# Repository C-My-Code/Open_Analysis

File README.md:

<!--
SPDX-FileCopyrightText: 2026 Open_Analysis contributors
SPDX-License-Identifier: GPL-3.0-or-later
-->

# Open_Analysis

Open_Analysis is an open-source (GPL-3.0-or-later) analysis suite for KiCad printed circuit boards, with Altium boards supported through import. It covers trace impedance, rule and EMI checks, DC IR drop, and 3D full-wave S-parameters. Signal-integrity (SI) channels, AC power integrity (PI), thermal analysis and EMC pre-compliance are planned.

It is built to answer one question before you pay for fabrication or a compliance test: **how likely is this design to meet its spec?** Every result carries an accuracy class and a stated error, so you can judge how far to trust it. See [How to read results](docs/CONFIDENCE.md).

## Status

Status follows [docs/ROADMAP.md](docs/ROADMAP.md). **Available** means the code runs today and its validation results are on the [validation page](docs/validation/index.md). It does not mean every validation case is closed; open gaps are listed in the next section.

| Feature | Status | Notes |
|---|---|---|
| KiCad 7 to 10 board ingest (`.kicad_pcb`), IPC-2581 ingest | Available | Altium and others through `kicad-cli pcb import` |
| Closed-form trace impedance, 2D BEM, 2D FEM reference | Available | `oa impedance xs`, `oa impedance profile` |
| ERC / EMI rule engine (21 rules registered) | Available | One known validation gap, see below |
| DC IR drop (`pi.dc`) | Available | One rail plus return; multi-rail trees are not done |
| 3D S-parameters with openEMS | Available | Needs openEMS installed. Validated 1 to 10 GHz (microstrip) and 4 to 20 GHz (via) only |
| 3D S-parameters with Palace | In progress | Adapter exists. Its validation cases are pending (WP-301) |
| Own GPU FDTD engine (`oa-fdtd`) | In progress | M1P, gated by [BENCHMARKS.md](docs/BENCHMARKS.md); B-PERF-01 has no engine result yet |
| GPU acceleration (`oa-accel`) | In progress | CuPy backend with a CPU fallback |
| Web UI, REST server, MCP server for AI agents | Available (partly) | Several UI views are not done; see [docs/FOLLOWUPS.md](docs/FOLLOWUPS.md) |
| Linear SI channels (IL/RL/TDR), crosstalk | Planned (M2) | |
| AC PDN, thermal, quasi-static 3D extraction | Planned (M2) | |
| EMC pre-compliance (MIL-STD-461, FCC, CISPR, DO-160) | Planned (M2) | [ADR-0011](docs/adr/0011-emc-compliance-prediction.md) |
| Uncertainty quantification, P(pass) | Planned (M2) | [ADR-0012](docs/adr/0012-uncertainty-quantification.md) |
| KiCad live plugin | Planned (M2) | |

The M1 release is held until the M1P benchmark gates pass (ROADMAP, "M1P").

## Why trust it

The approach is to check every solver against something that is not the solver:

1. **Analytic references** (exact formulas, constructions with a known answer).
2. **Published values** from cited papers, books and standards.
3. **Independent solvers** (BEM against FEM, openEMS against our BEM, one ingest reader against another).
4. **Measured data.** None exists yet.

Rules the validation page follows:

- Every number is produced by `tools/validation/run_validation.py` and stored in [`docs/validation/results.json`](docs/validation/results.json). Nothing is typed by hand.
- Cases whose reference came from this project's own code are labelled *self-computed* and are never counted as independent validation.
- Cases whose citation could not be checked are marked `[verify]` and are excluded from pass counts.
- Known gaps are listed, not hidden. They do not count as passed.

Read: the [validation page](docs/validation/index.md) (also as [HTML](docs/validation/validation.html)), the [benchmark gates](docs/BENCHMARKS.md) and the [known gaps](docs/FOLLOWUPS.md).

### Measured accuracy today

From the run of 2026-10-29 (commit `0cc834dc47ea`, Windows 11, Python 3.13.14; 264 cases: 248 pass, 0 fail, 3 known gap, 2 `[verify]`, 11 pending). "Error" is the absolute difference to the reference, as a percentage unless stated.

| Analysis | Reference | Cases passed | Error (max; median) | Open gap |
|---|---|---|---|---|
| Impedance, closed form and BEM | analytic (Cohn, CPW, wire over plane and others) | 59 (45 with an independent reference) | 0.23 %; 0.02 % (Z0 and eps_eff) | none |
| Impedance, BEM vs 2D FEM | cross-solver (shares the quasi-static model) | 123 of 124 | 0.43 %; 0.06 % | eps_eff on narrow high-er microstrip is 0.58 % off against a 0.5 % spec |
| Impedance, published | IPC-2141 microstrip example | 1 independent pass | 0.06 % (36.82 vs 36.8 ohm) | Polar SI9000, Wadell, Bryant-Weiss tables are pending |
| DC IR, analytic | strip, annulus, via barrel, via array, `power_strip` | 6 of 6 | 0.57 % (via barrel, 1 % tolerance); others 0.06 % or less | `kicad-irdrop` cross-check pending |
| DC IR, raster vs FEM | cross-solver | 3 of 4 | 0.68 % to 0.78 % | as above |
| ERC | one synthetic board per rule | 11 of 12 | exact match | IM-002 on three test boards: the boards miss their own impedance targets |
| Ingest | KiCad vs IPC-2581 readers, counts and areas | 33 of 33 | exact | per-net copper-area checks are partial |
| openEMS microstrip Z0 | our BEM, thin-strip copper | pass | -0.43 % (tolerance 3 %) | against BEM with real 35 um copper: +4.1 %, a **known gap** (openEMS uses sheet copper) |
| openEMS insertion loss, 23 mm microstrip, 10 GHz | our BEM RLGC cascade | pass | 0.089 dB (0.78 vs 0.69 dB; tolerance 0.2 dB) | the M1P target is 0.05 dB |
| Palace, openEMS vs Palace via transition | cross-solver | not run | - | pending WP-301 |

What this table does not say:

- Agreement between BEM and FEM tests the numerics, not the quasi-static assumption both share.
- No result has been compared with a physical measurement yet.
- Material data, tolerances and the stack-up are not in these numbers. See [docs/CONFIDENCE.md](docs/CONFIDENCE.md).

## Install

Requirements:

- Python 3.11 or newer. The repository pins no upper bound; the validation run used 3.13.
- [uv](https://docs.astral.sh/uv/).

```text
git clone <this repository>
cd Open_Analysis
uv sync --all-packages
uv run oa --help
```

### Optional: GPU

GPU support is an extra of the `oa-accel` package and is never a hard dependency. Without it everything runs on the CPU.

```text
uv sync --all-packages --extra cuda12      # NVIDIA, CUDA 12 (cupy-cuda12x, nvmath-python)
```

Extras defined in `packages/oa-accel/pyproject.toml`: `cuda12`, `cuda13`, `rocm`. The extra commands above are not verified on a GPU machine here. Check what was found with `uv run oa-accel-doctor`.

AMD ROCm (`amd-cupy`) is **untested on hardware**. Set `OA_DEVICE=cpu` to force the CPU path.

### Optional: external tools

| Tool | Needed for | Notes |
|---|---|---|
| KiCad 10 (`kicad-cli`) | Altium and other import, DRC, optional zone refill | Found automatically in the usual locations (for example `D:\Program Files\KiCad\*\bin` on Windows, `/usr/bin` on Linux), or set in `tools.toml` |
| openEMS (0.37.x) and its Python bindings | `em.sparams --solver openems` | Run as a separate process, never imported. Path comes from `tools.toml` |
| Palace 0.18.x | `em.sparams --solver palace` | Run in WSL2 or Linux. Build with [`docker/palace/install-wsl.sh`](docker/palace/install-wsl.sh) (no sudo, about 40 minutes, 5 GB of disk), or use [`docker/palace/Dockerfile`](docker/palace/Dockerfile) |

Run `uv run oa doctor` for an offline report of what was found (Python, WSL, Docker, KiCad, gmsh and others). On the machine used to check this README, `oa doctor` found KiCad 10.0.5 and gmsh 4.15.2; openEMS was not installed, so the openEMS solve is not demonstrated below.

### Platform notes

- **Windows (native):** the primary development platform. openEMS runs natively. Palace needs WSL2 or Docker. Process memory is capped by a job object (see TASKS.md, rule 10).
- **Linux:** Palace builds natively with the same script. Tests run on Linux in CI.
- **macOS:** supported for the pure-Python core (ROADMAP: macOS CI covers the core). GPU and external-solver paths are not tested there.

## Quick start

All commands below were run on this repository's test boards. `--json` is an option of each subcommand (write `oa erc --json`, not `oa --json erc`). It prints one envelope: `{schema, version, ok, data, warnings, errors}`.

```text
BOARD=tests/boards/kicad10/microstrip/board.kicad_pcb
```

**Open a board and read it**

```text
uv run oa open $BOARD
uv run oa board summary -p $BOARD
uv run oa board nets -p $BOARD
```

`oa open` returns a `project_id` and a summary. A bare board file opens an ephemeral project and writes nothing next to it. Lengths are in metres.

**Impedance**

```text
uv run oa impedance xs --quick '{"topology":"microstrip","w":"5mil","h":"4mil","t":"1.4mil","er":4.2}'
uv run oa impedance profile -p $BOARD --nets '{"names":["MS_250"]}'
```

The first is the `oa describe` example: a closed-form Hammerstad-Jensen microstrip, which prints Z0 = 58.66 ohm. The second samples net `MS_250` along its route and prints a summary with a `result_id`. Check `accuracy_class` before quoting a number.

**ERC**

```text
uv run oa erc -p $BOARD
uv run oa results summary <result_id>
```

The microstrip board gives 0 violations from 21 rules. Results are stored, so `oa results summary` works from a later command. Use `--fail-on error` for a CI exit code.

**DC IR drop** (on the `power_strip` board, a 50 x 5 mm L1 strip, analytic R = 4.926 mohm)

```text
POWER=tests/boards/kicad10/power_strip/board.kicad_pcb
uv run oa run -p $POWER --analysis pi.dc --config '{"rail":{"net":"STRIP"},"vrm":{"component":"J1","vset":1.0},"loads":[{"component":"J2","current":1.0}]}'
```

This reports the worst load drop and the V, dV and J_mag fields. Run `oa describe --analyses` for the full config schema.

**S-parameters** (3D full wave)

```text
uv run oa run -p $BOARD --analysis em.sparams --dry-run --config '{"solver":"openems","region":{"nets":["MS_250"],"reference_nets":["GND"]},"frequency":{"f_min":1e9,"f_max":1e10,"n_points":50}}'
```

`--dry-run` validates the setup and prints an estimate (3 tasks, about 184 s of work, 1.3 GB peak memory, needs `openems-python`). Remove `--dry-run` to run it once openEMS is installed. The solve itself was not run for this README. Frequencies are numbers in Hz in this form. Output is a Touchstone file that passes a passivity, causality and DC quality gate before it is reported as good.

**Discover everything**

```text
uv run oa describe                 # every command, schema id, side effect, example
uv run oa describe --analyses      # installed analyses with config schemas
uv run oa schema                   # published JSON Schema ids
```

### Web UI

```text
uv run oa serve                    # local REST server and web UI; --port, --host, --no-browser
```

The server binds to 127.0.0.1 with a random bearer token. The front end lives in `web/` (see `web/README.md`). Several result views (TDR, Smith chart, 3D preview) are not done, see FOLLOWUPS.

### Connect an AI agent (MCP)

```text
claude mcp add open-analysis -- uv --directory /path/to/Open_Analysis run oa-mcp --root /path/to/projects
```

`oa-mcp` is a thin adapter over the same command catalog as the CLI. It is read-only unless you ask for a `write` command, and writes go through propose then apply. It makes no network calls; only `oa-assistant` (off by default) may. Details for Claude Code, Claude Desktop and others: [docs/agents/connect.md](docs/agents/connect.md). How an agent should work and state accuracy: [docs/agents/AGENTS.md](docs/agents/AGENTS.md), [docs/agents/accuracy.md](docs/agents/accuracy.md).

## Project layout

```text
packages/    Python packages (uv workspace), layered per docs/ARCHITECTURE.md
  oa-model, oa-framework, oa-geometry, oa-physics, oa-mesh      model and core services
  oa-ingest-kicad, oa-ingest-ipc2581, oa-kicad-bridge           board readers
  oa-impedance, oa-erc, oa-pi, oa-si, oa-thermal, oa-qs, oa-emi analyses (some are skeletons)
  oa-em, oa-em-openems, oa-em-palace, oa-fdtd, oa-accel         3D solvers and GPU backend
  oa-network, oa-results, oa-jobs, oa-service                   S-parameter tools, results, jobs, command catalog
  oa-cli, oa-server, oa-mcp, oa-assistant                       adapters (CLI, REST, MCP, optional AI assistant)
  oa-native, oa-testkit, oa-devguard                            Rust core, test fixtures, dev memory guard
web/         web UI
crates/      Rust sources for oa-native
schemas/     published JSON Schemas
tests/       tests, golden data (tests/golden), test boards (tests/boards)
docs/        architecture, specs, ADRs, roadmap, validation, agent docs
tools/       validation, benchmark and board-generation scripts
docker/      Palace build files
```

Key documents: [ARCHITECTURE](docs/ARCHITECTURE.md), [ROADMAP](docs/ROADMAP.md), [TASKS](docs/TASKS.md), [BENCHMARKS](docs/BENCHMARKS.md), [specs](docs/specs/), [ADRs](docs/adr/).

## Contributing

Read [CLAUDE.md](CLAUDE.md) (or [AGENTS.md](AGENTS.md)) and [docs/TASKS.md](docs/TASKS.md). The rules are binding: owned paths per work package, frozen contracts, SPDX headers on every new file, and a DCO sign-off on every commit.

```text
uv run pytest -m "not external"
uv run ruff check . && uv run ruff format --check .
uv run mypy
uv run lint-imports
uv run reuse lint
```

## License

GPL-3.0-or-later ([LICENSE](LICENSE), [ADR-0001](docs/adr/0001-license-gpl3.md)). The JSON Schemas (`schemas/`), test boards and fixtures (`tests/boards/`, `tests/fixtures/`) and `examples/` are dual-licensed `CC-BY-4.0 OR GPL-3.0-or-later`: recipients choose either (ADR-0001, `REUSE.toml`). Code stays GPL-3.0-or-later.

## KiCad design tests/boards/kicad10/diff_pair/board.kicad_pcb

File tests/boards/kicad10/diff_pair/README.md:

# diff_pair

6-layer board. One 100 ohm class edge-coupled pair DP_P/DP_N: L1 microstrip (3 mm uncoupled breakout, 0.4 mm length mismatch bump), a blind via pair with 4 GND return vias, L3 stripline with a gap step, a second via pair with 4 return vias, and L1 pads.

## Files

- `board.kicad_pcb`, `board.kicad_pro`: the board (KiCad 10 syntax, generated with KiCad 10.0.5).
- `expected.yaml`: ground truth for the readers and analyses (schema: `../expected.schema.json`).
- `drc.json`: `kicad-cli pcb drc --format json --severity-all` output.
- `board.ipc2581.xml`: IPC-2581 rev C export, `board.odb.zip`: ODB++ export, `board.png`: 3D render.

## Deliberate features and their rules

| Rule | Nets | Layer | Location (mm, file frame) | Created by |
|---|---|---|---|---|
| DP-001 | DP_P, DP_N | L1 | 11.500, 15.000 | `boardgen.features.diff_pair` |
| DP-002 | DP_P, DP_N | L1 | - | `boardgen.features.diff_pair` |
| DP-003 | DP_P, DP_N | L3 | 72.500, 15.000 | `boardgen.features.diff_pair` |

## KiCad DRC

0 errors, 0 warnings (`drc.json`). By type: `{}`.

## Regenerate

```
python tools/boardgen/build_all.py --only diff_pair
```

Licence: CC-BY-4.0 (see the `.license` sidecars).

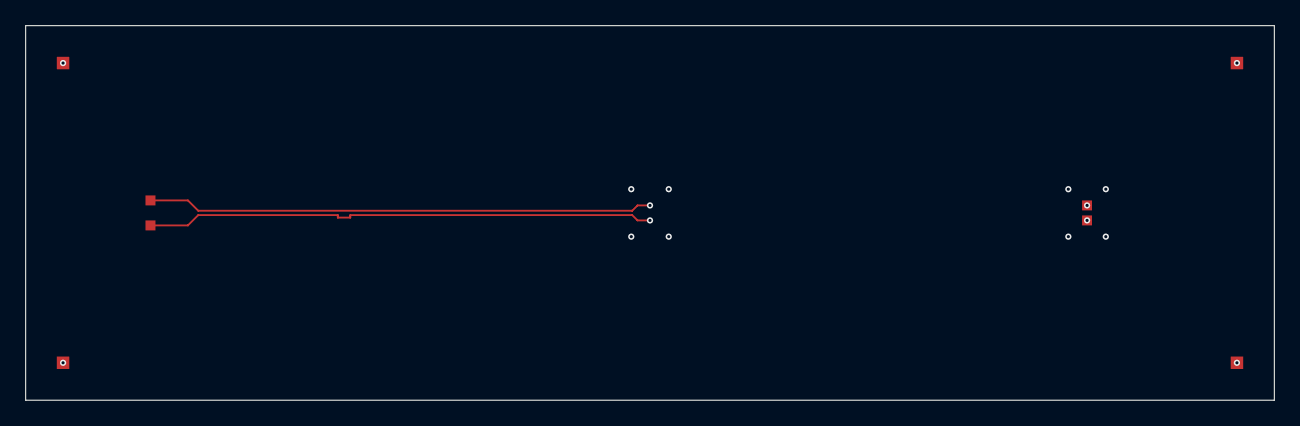
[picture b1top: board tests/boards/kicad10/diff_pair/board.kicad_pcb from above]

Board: 6 copper layers, 100.0 x 30.0 mm, 8 parts (0 on the bottom side), 3 nets.

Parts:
TP1, TP2, TP3, TP4, TP5, TP6, TP7, TP8: OA_Test:Pad; Pad

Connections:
DP_N: TP6.1, TP8.1
DP_P: TP5.1, TP7.1
GND: TP1.1, TP2.1, TP3.1, TP4.1

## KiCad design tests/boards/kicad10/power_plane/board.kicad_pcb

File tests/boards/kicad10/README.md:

# Synthetic KiCad 10 test boards (WP-102)

Eleven small boards with known geometry, written by `tools/boardgen/` and refilled, checked and exported with
KiCad 10.0.5. They are the ground truth for the KiCad reader (WP-101), the IPC-2581 reader (WP-103), the ERC rules
(WP-201), impedance/profile/DC/EM tests and the web viewer. All are FR-4-like (Dk 4.3, Df 0.02), 35 um copper, no
solder mask, with a known stackup. Licence: CC-BY-4.0 (`*.license` sidecars); the generator is GPL-3.0-or-later.

| Directory | Layers | Purpose |
|---|---|---|
| `microstrip` | 4 (1.6 mm) | 3 L1 microstrips (0.25/0.35/0.5 mm, 50 mm, h = 0.2 mm), launch pads; IM-002 on the 0.25 and 0.5 mm traces |
| `microstrip_v9` | 4 | Same copper in KiCad 9 syntax (net table, numeric item nets, version 20241229) |
| `stripline` | 6 | Symmetric stripline on L3, offset stripline on L4 (L3 empty above, L5 GND below) |
| `diff_pair` | 6 | 100 ohm pair: L1 microstrip, blind via pair + 4 return vias, L3 stripline; DP-001/002/003 |
| `cpwg` | 4 | CPWG (S 0.3, G 0.15, h 0.2) with two via fences (RF-001 on the 3x pitch) |
| `split_plane` | 4 | RP-001/002/003/007, ED-001/002 |
| `via_transition` | 8 (2.0 mm) | Stub (VI-001), backdrill, via pair with returns, transition without return (RP-004), blind/buried/micro vias |
| `power_plane` | 4 | L3 +1V0 plane 40 x 30 mm, VRM U5, load U1 (32 pins), decaps C1 (1.5 mm) and C2 (12 mm): PD-001; EM-011 cavity |
| `power_strip` | 4 | 50 x 5 mm strip, analytic R = Rs L / W |
| `power_two_layer_vias` | 4 | Two 20 x 20 mm squares joined by 9 vias, analytic via-array R |
| `combined` | 8 | Everything above in separate regions, net classes `50ohm`/`90ohm`/`100ohm`, `USB_D+`/`USB_D-` |

Every directory holds `board.kicad_pcb`, `board.kicad_pro`, `board.ipc2581.xml` (IPC-2581 rev C),
`board.odb.zip`, `board.png` (3D render), `drc.json`, `expected.yaml` and a `README.md`.

## Regenerate

```
python tools/boardgen/build_all.py                 # all boards (needs KiCad 10.0.5; set OA_KICAD_DIR if not in the default place)
python tools/boardgen/build_all.py --only cpwg     # one board
python tools/boardgen/validate_expected.py         # schema + consistency check (needs pyyaml, jsonschema)
```

Output is deterministic: uuids come from `uuid5(board, kind, counter)` and timestamps are scrubbed, so two runs
give byte-identical `board.kicad_pcb`, `board.kicad_pro`, `drc.json`, `expected.yaml` and `README.md`. The IPC-2581 and
ODB++ exports are KiCad output whose element order (pads within a package, for example) varies from run to run; they
are equal as data, not as bytes, so compare them by parsing. `.gitattributes` here disables line-ending conversion.

## `expected.yaml` (schema: `expected.schema.json`, id `oa-board-expected/1`)

All physical quantities are SI (m, m^2, Hz, S/m, ohm). Exceptions, named `*_mm`: positions and tolerances in millimetres
in the **KiCad file frame (Y down)**; the Y-up board model uses `y_model = -y_file`. Layer ids are canonical (`L1` = top
copper, `D1` = first dielectric, top to bottom); `source_layer`/`source_name` give the KiCad name. z = 0 is the bottom face
of the lowest copper layer.

| Key | Content |
|---|---|
| `kicad` | syntax flavour (10/9), file version, whether a net table exists |
| `materials` | Dk, Df, copper thickness, conductivity (5.8e7 S/m, the model default) |
| `counts` | nets, vias per kind (`through`/`blind`/`buried`/`micro`), pads (smd/tht), tracks, arcs, zones, rule areas (copper-pour keepouts), footprints, copper layers. Measured by pcbnew after the refill and asserted equal to the generator's own count |
| `stackup` | `board_thickness` and per-layer `thickness`, `z_bottom`, `z_top` (exact to 1 nm) |
| `copper_area` | per layer, per net, m^2, computed by pcbnew after `ZONE_FILLER` (union of fills, tracks, pads, via pads); tolerance 0.1 % |
| `nets`, `net_classes`, `net_class_patterns`, `diff_pairs` | net names, `.kicad_pro` classes/patterns, pair membership (`origin`: `naming`) |
| `geometry` | named dimensions per feature (widths, lengths, gaps, via spans, stub lengths, plane outlines, ...) |
| `erc` | violations that MUST be reported: `rule_id`, `nets`, `layer`, `location_mm` (null = whole-net result), `tolerance_mm`, `generator` (the `boardgen.features.*` function that created the feature) and `why` |
| `must_not_report` | catalogue rules that must not fire anywhere on the board |
| `negative_cases` | specific places that look similar but are compliant (a test may assert no report there) |
| `unspecified` | cases where the result depends on rule thresholds; tests must not assert either way |
| `intended_drc` | KiCad DRC **errors** that are deliberate (empty on every board) |
| `drc` | counts and types of all DRC results, including warnings |
| `dc` | analytic resistances with formula and tolerance (`power_strip`, `power_two_layer_vias`) |
| `em` | EM-011 cavity frequencies and suggested ports (`power_plane`) |

## Using KiCad on these boards

DRC: `kicad-cli pcb drc --format json --severity-all board.kicad_pcb` returns exit code 0 and 0 errors on every board.
Remaining warnings are `via_dangling` (isolated buried/blind/micro vias that exist only to exercise the reader and the
swiss-cheese antipads). Loading a board with `pcbnew.LoadBoard` from Python can block on a wx assertion dialog for
some inputs (seen with the KiCad 9 syntax file); always run such helpers with a timeout.

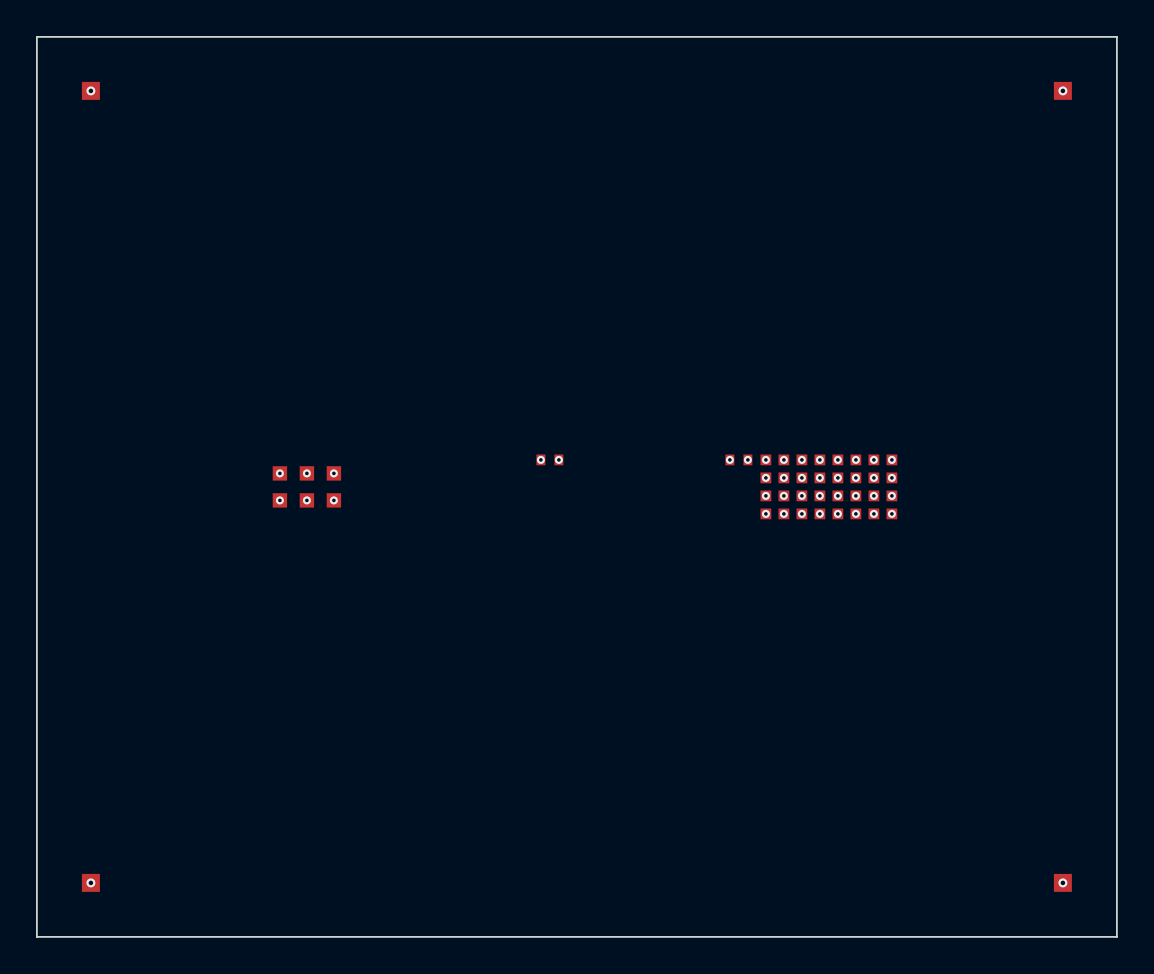
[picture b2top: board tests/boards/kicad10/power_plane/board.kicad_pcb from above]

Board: 4 copper layers, 60.0 x 50.0 mm, 8 parts (0 on the bottom side), 2 nets, no tracks yet.

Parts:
C1, C2: OA_Test:C_0402; C_0402
TP1, TP2, TP3, TP4: OA_Test:Pad; Pad
U1: OA_Test:Load_8x4; Load_8x4
U5: OA_Test:VRM_3out; VRM_3out

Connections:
+1V0: C1.2, C2.2, U1.1, U1.3, U1.6, U1.8, U1.9, U1.11, U1.14, U1.16, U1.17, U1.19, U1.22, U1.24, U1.25, U1.27, U1.30, U1.32, U5.1, U5.2, U5.3
GND: C1.1, C2.1, TP1.1, TP2.1, TP3.1, TP4.1, U1.2, U1.4, U1.5, U1.7, U1.10, U1.12, U1.13, U1.15, U1.18, U1.20, U1.21, U1.23, U1.26, U1.28, U1.29, U1.31, U5.4, U5.5, U5.6

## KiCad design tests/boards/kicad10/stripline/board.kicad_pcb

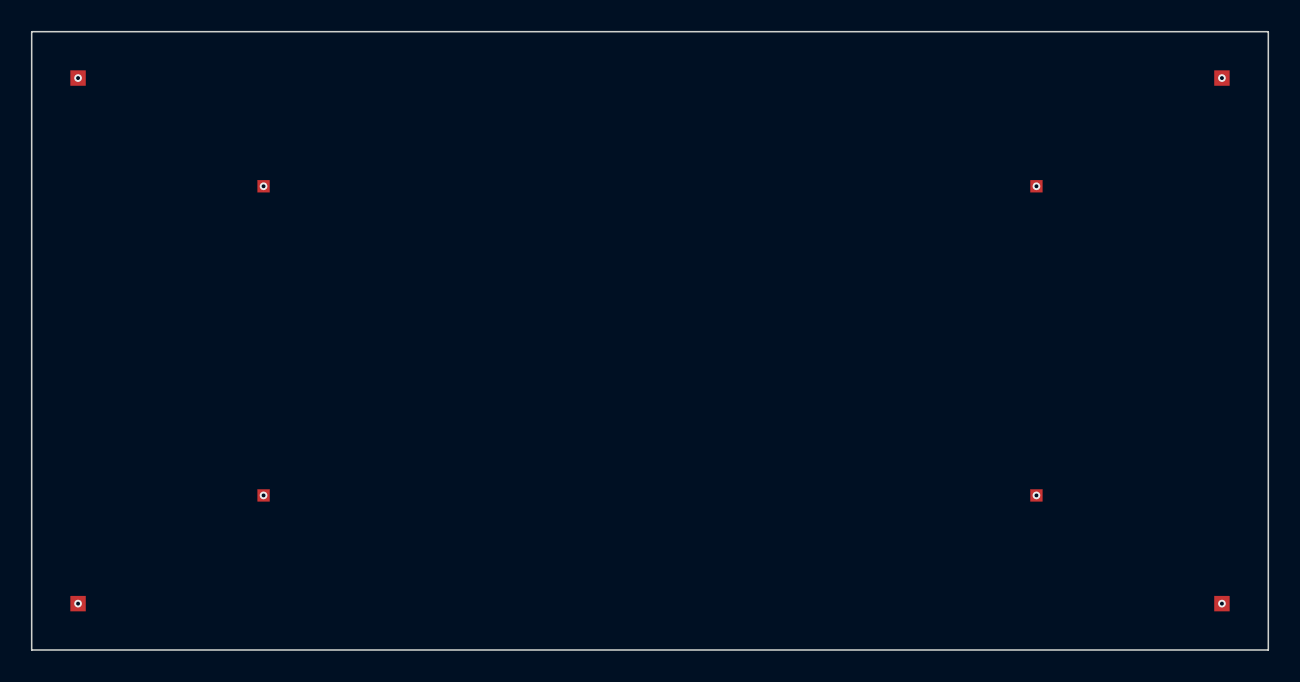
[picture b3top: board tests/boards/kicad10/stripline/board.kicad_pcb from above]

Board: 6 copper layers, 80.0 x 40.0 mm, 8 parts (0 on the bottom side), 3 nets.

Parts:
TP1, TP2, TP3, TP4, TP5, TP6, TP7, TP8: OA_Test:Pad; Pad

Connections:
GND: TP1.1, TP2.1, TP3.1, TP4.1
SL_OFF: TP7.1, TP8.1
SL_SYM: TP5.1, TP6.1

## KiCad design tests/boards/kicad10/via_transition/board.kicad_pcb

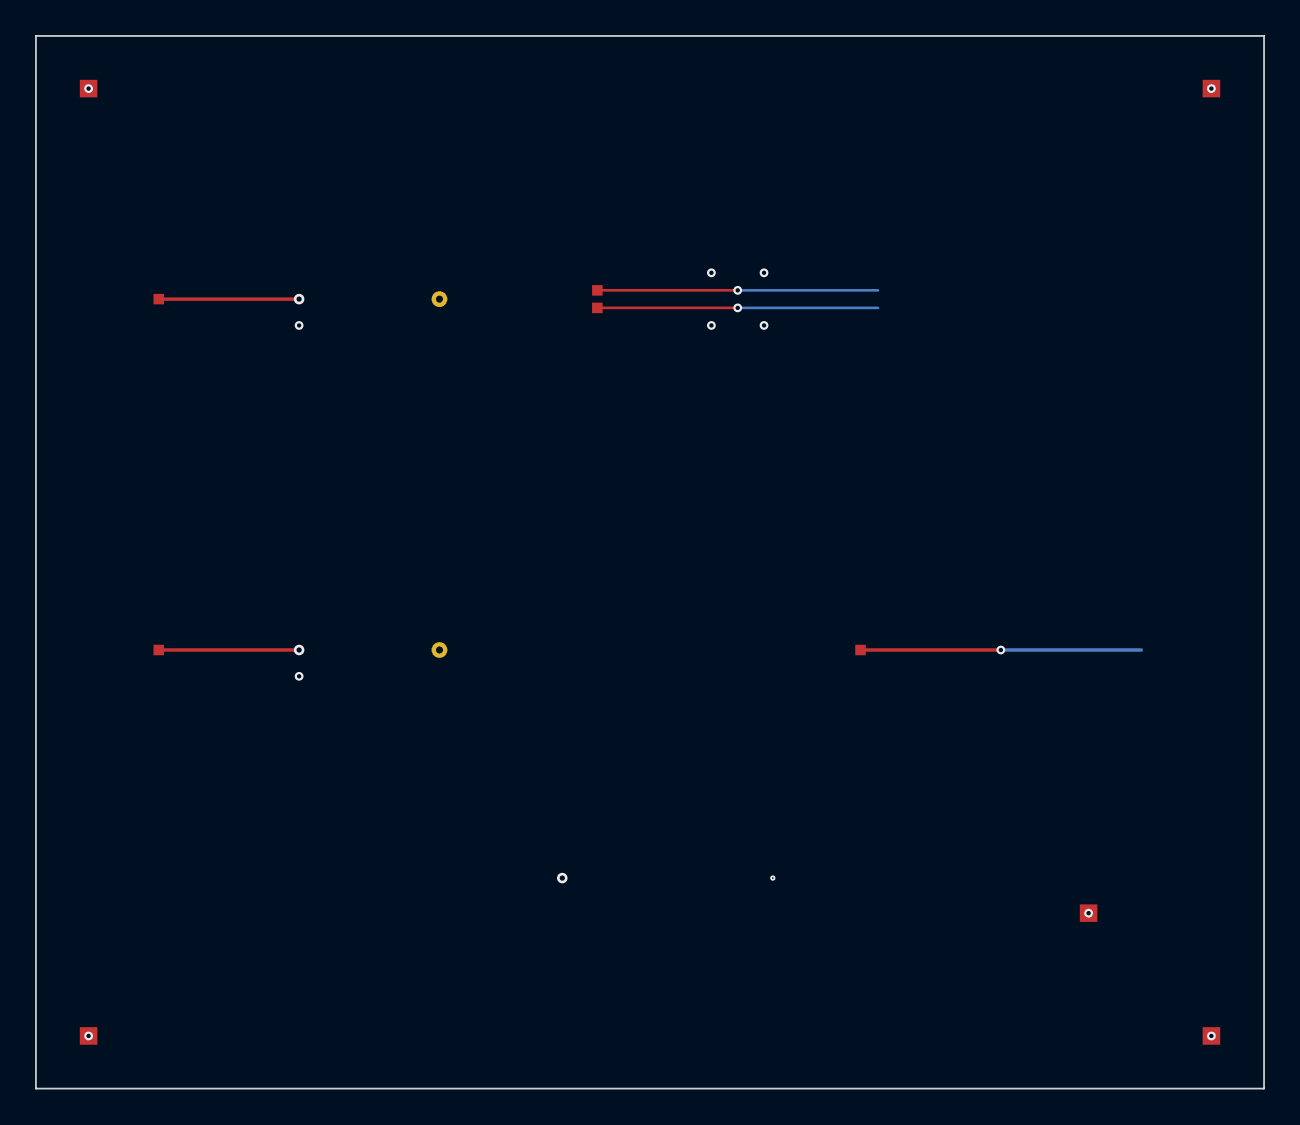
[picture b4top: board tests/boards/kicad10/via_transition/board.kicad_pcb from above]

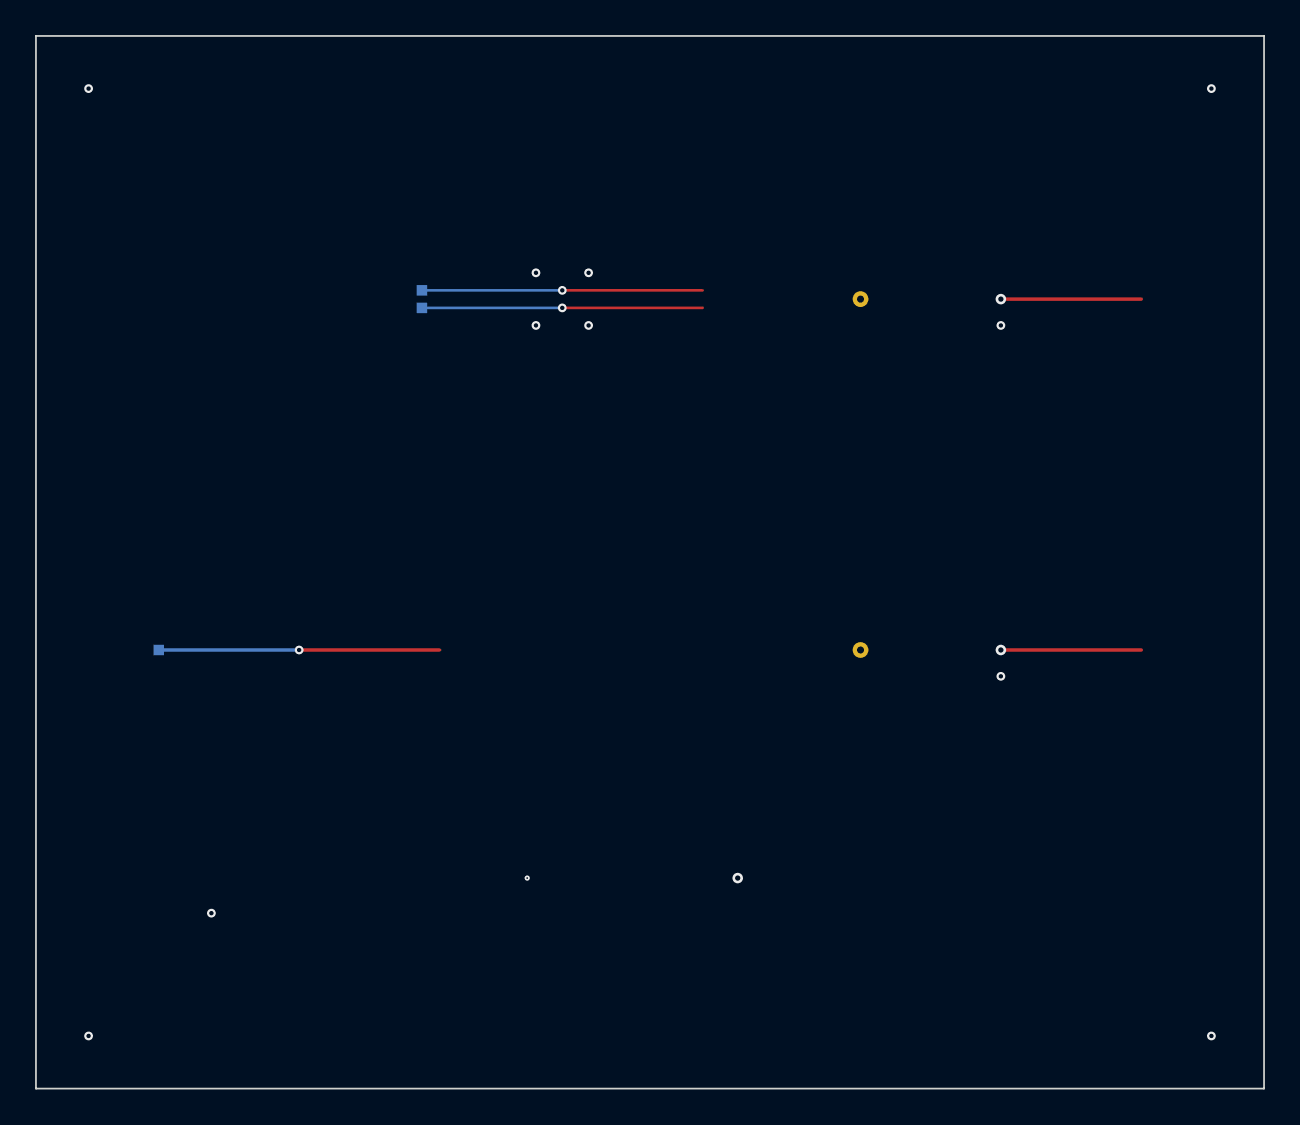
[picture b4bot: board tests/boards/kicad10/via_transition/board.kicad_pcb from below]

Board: 8 copper layers, 70.0 x 60.0 mm, 15 parts (3 on the bottom side), 6 nets.

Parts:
TH1, TH2: OA_Test:Pad; Pad
TP1, TP2, TP3, TP4, TP5, TP6, TP7, TP8, TP9, TP10, TP11, TP12, TP13: OA_Test:Pad; Pad

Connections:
GND: TP1.1, TP2.1, TP3.1, TP4.1
NR: TP12.1, TP13.1
SE1: TH1.1, TP6.1
SE2: TH2.1, TP7.1
VD_N: TP10.1, TP11.1
VD_P: TP8.1, TP9.1

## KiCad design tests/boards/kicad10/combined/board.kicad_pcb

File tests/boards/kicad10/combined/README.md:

# combined

8-layer 2.0 mm board carrying every violation of the other boards in separate regions, plus net classes 50ohm / 90ohm / 100ohm and the USB_D+ / USB_D- pair. L2/L4/L7 GND planes, L5 +1V0 plane (full board).

## Files

- `board.kicad_pcb`, `board.kicad_pro`: the board (KiCad 10 syntax, generated with KiCad 10.0.5).
- `expected.yaml`: ground truth for the readers and analyses (schema: `../expected.schema.json`).
- `drc.json`: `kicad-cli pcb drc --format json --severity-all` output.
- `board.ipc2581.xml`: IPC-2581 rev C export, `board.odb.zip`: ODB++ export, `board.png`: 3D render.

## Deliberate features and their rules

| Rule | Nets | Layer | Location (mm, file frame) | Created by |
|---|---|---|---|---|
| RP-001 | SIG_SLOT | L1 | 50.000, 15.000 | `boardgen.features.split_plane` |
| ED-001 | SIG_PLEDGE | L1 | 30.000, 51.750 | `boardgen.features.split_plane` |
| RP-007 | SIG_NOREF | L1 | 75.000, 56.000 | `boardgen.features.split_plane` |
| RP-002 | SIG_SWISS | L1 | 20.000, 30.000 | `boardgen.features.split_plane` |
| RP-003 | SIG_REFCHG | L1 | 75.000, 35.000 | `boardgen.features.split_plane` |
| ED-002 | SIG_BOARDEDGE | L1 | 0.400, 25.000 | `boardgen.features.split_plane` |
| IM-002 | MS_250 | L1 | 135.000, 10.000 | `boardgen.features.microstrip` |
| IM-002 | MS_500 | L1 | 135.000, 30.000 | `boardgen.features.microstrip` |
| RF-001 | CPW_B | L1 | 195.000, 30.000 | `boardgen.features.cpwg` |
| VI-001 | SE1 | L6 | 15.000, 90.000 | `boardgen.features.via_transition` |
| RP-004 | NR | L1 | 55.000, 110.000 | `boardgen.features.via_transition` |
| DP-001 | DP_P, DP_N | L1 | 81.500, 100.000 | `boardgen.features.diff_pair` |
| DP-002 | DP_P, DP_N | L1 | - | `boardgen.features.diff_pair` |
| DP-003 | DP_P, DP_N | L3 | 142.500, 100.000 | `boardgen.features.diff_pair` |
| PD-001 | +1V0 | L1 | 198.500, 98.500 | `boardgen.features.power_loads` |

## Notes

- KiCad has no explicit diff-pair object: the Altium-style explicit pair is represented by the +/- naming and the 90ohm netclass pattern USB_D*.

## KiCad DRC

0 errors, 28 warnings (`drc.json`). By type: `{"warning": {"via_dangling": 28}}`.

## Regenerate

```
python tools/boardgen/build_all.py --only combined
```

Licence: CC-BY-4.0 (see the `.license` sidecars).

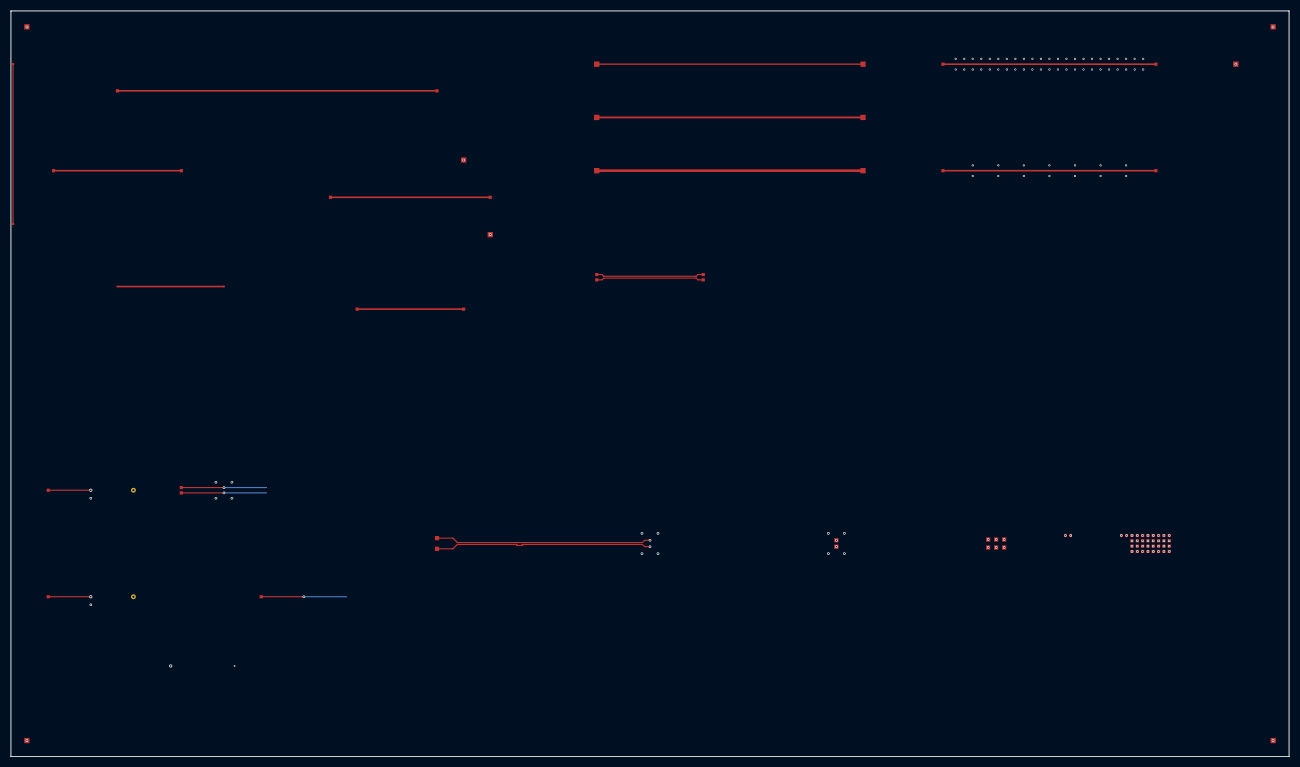
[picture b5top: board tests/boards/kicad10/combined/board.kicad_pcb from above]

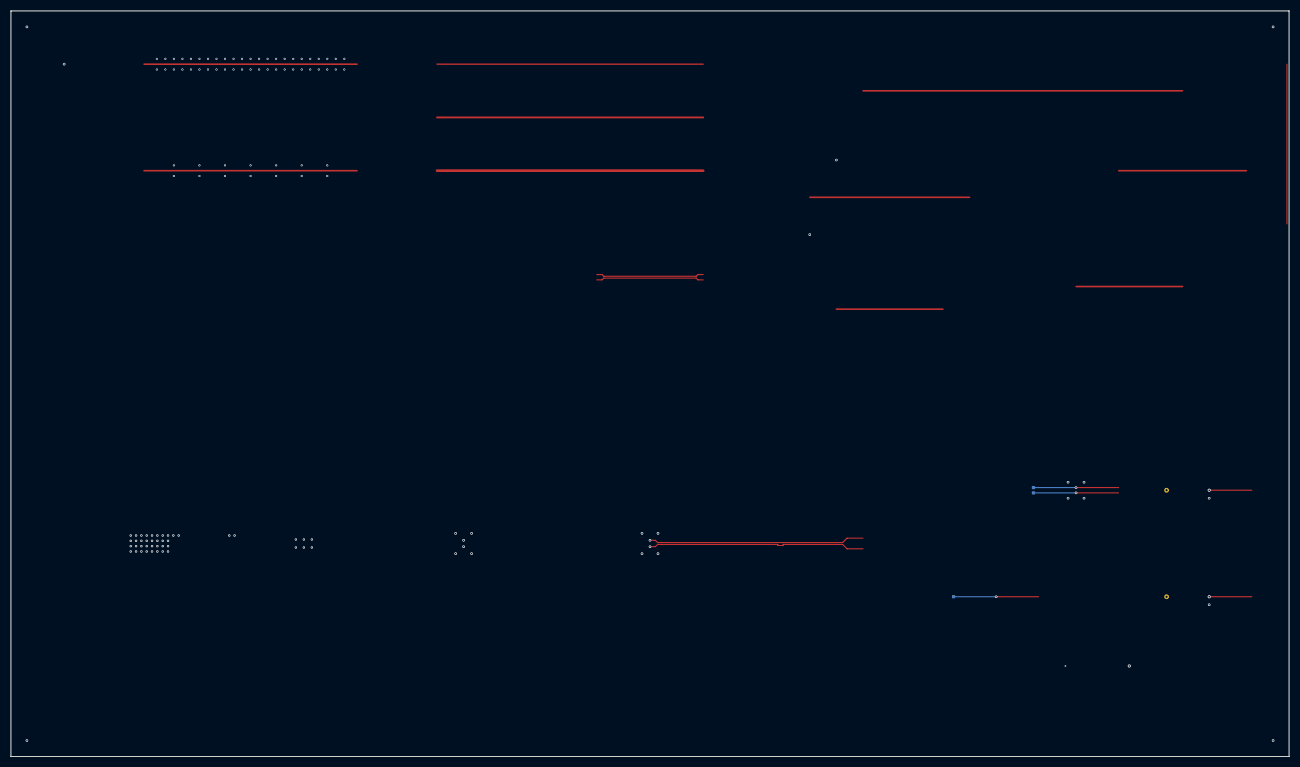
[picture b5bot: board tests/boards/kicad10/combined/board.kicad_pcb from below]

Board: 8 copper layers, 240.0 x 140.0 mm, 51 parts (3 on the bottom side), 23 nets.

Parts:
C1, C2: OA_Test:C_0402; C_0402
TH1, TH2: OA_Test:Pad; Pad
TP1, TP2, TP3, TP4, TP5, TP6, TP7, TP8, TP9, TP10, TP11, TP12, TP13, TP14, TP15, TP16, TP17, TP18, TP19, TP20, TP21, TP22, TP23, TP24, TP25, TP26, TP27, TP28, TP29, TP30, TP31, TP32, TP33, TP34, TP35, TP36, TP37, TP38, TP39, TP40, TP41, TP42, TP43, TP44, TP45: OA_Test:Pad; Pad
U1: OA_Test:Load_8x4; Load_8x4
U5: OA_Test:VRM_3out; VRM_3out

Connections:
+1V0: C1.2, C2.2, TP5.1, U1.1, U1.3, U1.6, U1.8, U1.9, U1.11, U1.14, U1.16, U1.17, U1.19, U1.22, U1.24, U1.25, U1.27, U1.30, U1.32, U5.1, U5.2, U5.3
+3V3: TP16.1, TP17.1
CPW_A: TP26.1, TP27.1
CPW_B: TP28.1, TP29.1
DP_N: TP43.1, TP45.1
DP_P: TP42.1, TP44.1
GND: C1.1, C2.1, TP1.1, TP2.1, TP3.1, TP4.1, U1.2, U1.4, U1.5, U1.7, U1.10, U1.12, U1.13, U1.15, U1.18, U1.20, U1.21, U1.23, U1.26, U1.28, U1.29, U1.31, U5.4, U5.5, U5.6
MS_250: TP20.1, TP21.1
MS_350: TP22.1, TP23.1
MS_500: TP24.1, TP25.1
NR: TP40.1, TP41.1
SE1: TH1.1, TP34.1
SE2: TH2.1, TP35.1
SIG_BOARDEDGE: TP18.1, TP19.1
SIG_NOREF: TP10.1, TP11.1
SIG_PLEDGE: TP8.1, TP9.1
SIG_REFCHG: TP14.1, TP15.1
SIG_SLOT: TP6.1, TP7.1
SIG_SWISS: TP12.1, TP13.1
USB_D+: TP30.1, TP31.1
USB_D-: TP32.1, TP33.1
VD_N: TP38.1, TP39.1
VD_P: TP36.1, TP37.1

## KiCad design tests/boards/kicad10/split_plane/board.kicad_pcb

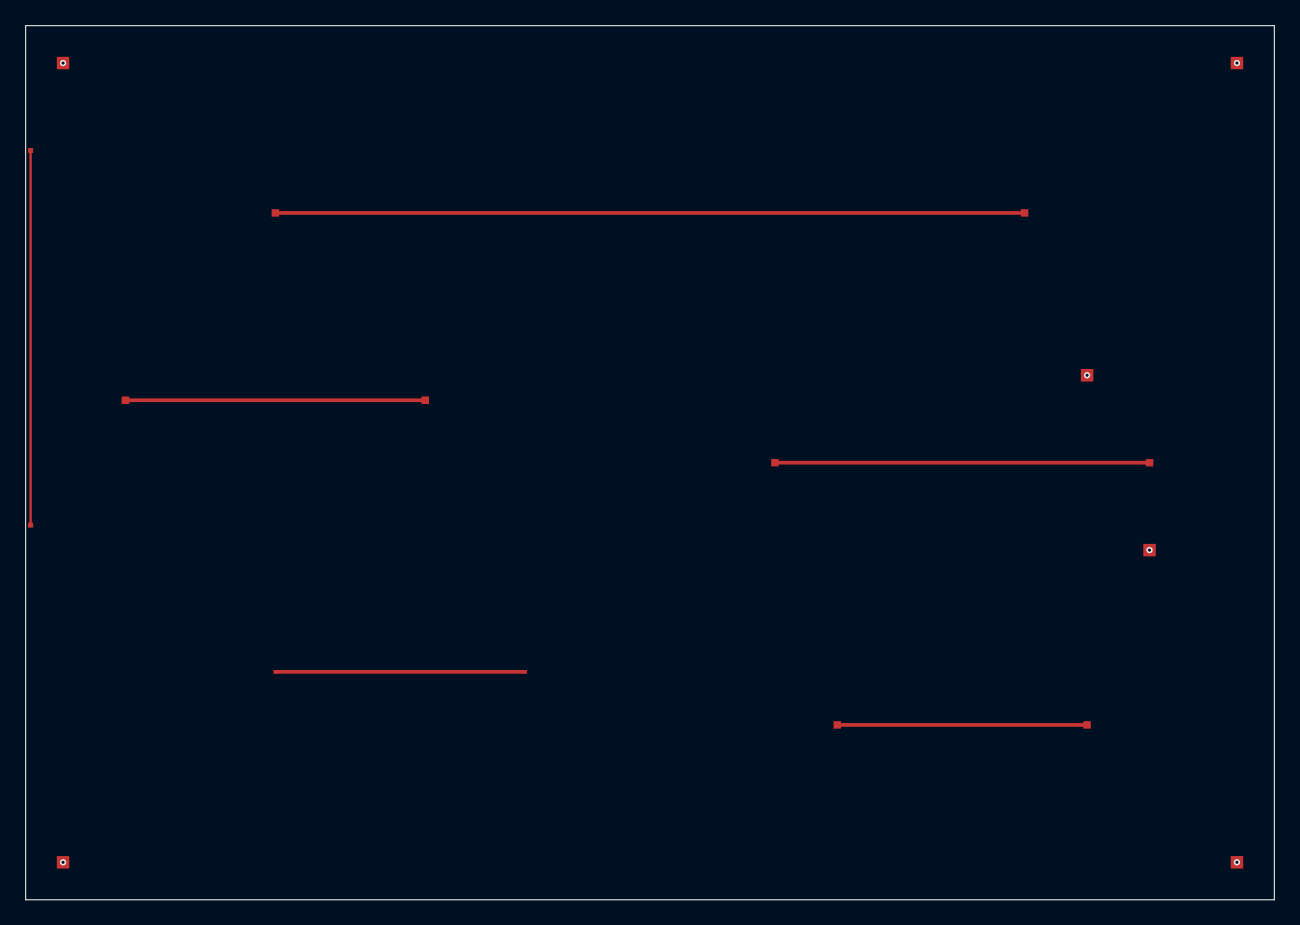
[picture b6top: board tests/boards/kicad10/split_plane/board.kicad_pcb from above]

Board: 4 copper layers, 100.0 x 70.0 mm, 18 parts (0 on the bottom side), 8 nets.

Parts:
TP1, TP2, TP3, TP4, TP5, TP6, TP7, TP8, TP9, TP10, TP11, TP12, TP13, TP14, TP15, TP16, TP17, TP18: OA_Test:Pad; Pad

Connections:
+3V3: TP15.1, TP16.1
GND: TP1.1, TP2.1, TP3.1, TP4.1
SIG_BOARDEDGE: TP17.1, TP18.1
SIG_NOREF: TP9.1, TP10.1
SIG_PLEDGE: TP7.1, TP8.1
SIG_REFCHG: TP13.1, TP14.1
SIG_SLOT: TP5.1, TP6.1
SIG_SWISS: TP11.1, TP12.1
